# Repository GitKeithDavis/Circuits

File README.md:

# Circuits
Open hardware circuit designs by Keith Davis.

# Licensing and More
Refer to the CERN Open Hardware License v1.2 (OHL) [copy] (cern_ohl_v_1_2.txt) in the root of this Git repo along with this [README] document for licensing, liability, and more.
  
Use of the content in this repo implies your consent to the OHL terms.  The original OHL v1.2 was found [here](<https://www.ohwr.org/project/cernohl/wikis/Documents/CERN-OHL-version-1.2>).

[//]: # (Hide links)

   [OHL]: <https://www.ohwr.org/project/cernohl/wikis/Documents/CERN-OHL-version-1.2>
   [copy]: <https://github.com/GitKeithDavis/Circuits/blob/master/cern_ohl_v_1_2.txt>
   [README]: <https://github.com/GitKeithDavis/Circuits/blob/master/README.md>

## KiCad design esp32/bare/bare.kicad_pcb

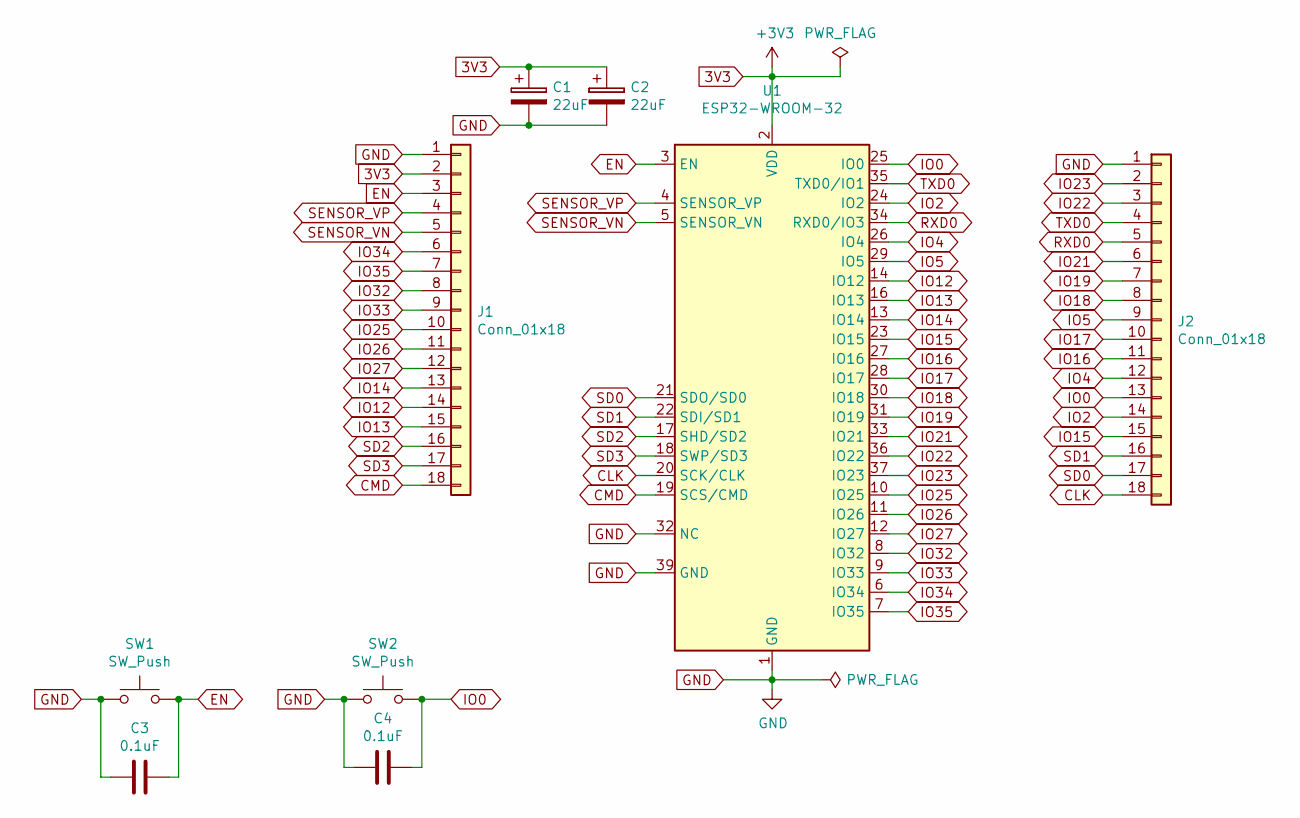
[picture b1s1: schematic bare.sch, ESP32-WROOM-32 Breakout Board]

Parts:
C1, C2: 22uF; C_0805_2012Metric
C3, C4: 0.1uF; C_0805_2012Metric
J1, J2: Conn_01x18; PinHeader_1x18_P2.54mm_Vertical
SW1, SW2: SW_Push; Button_Switch_Push_NO_LCSC_TS5215A160gf
U1: ESP32-WROOM-32

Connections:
3V3: C1.1, C2.1, J1.2, U1.2 (VDD)
CLK: J2.18, U1.20 (SCK/CLK)
CMD: J1.18, U1.19 (SCS/CMD)
EN: C3.1, J1.3, SW1.2, U1.3 (EN)
GND: C1.2, C2.2, C3.2, C4.2, J1.1, J2.1, SW1.1, SW2.1, U1.1 (GND), U1.15 (GND), U1.32 (NC), U1.38 (GND), U1.39 (GND)
IO0: C4.1, J2.13, SW2.2, U1.25 (IO0)
IO2: J2.14, U1.24 (IO2)
IO4: J2.12, U1.26 (IO4)
IO5: J2.9, U1.29 (IO5)
IO12: J1.14, U1.14 (IO12)
IO13: J1.15, U1.16 (IO13)
IO14: J1.13, U1.13 (IO14)
IO15: J2.15, U1.23 (IO15)
IO16: J2.11, U1.27 (IO16)
IO17: J2.10, U1.28 (IO17)
IO18: J2.8, U1.30 (IO18)
IO19: J2.7, U1.31 (IO19)
IO21: J2.6, U1.33 (IO21)
IO22: J2.3, U1.36 (IO22)
IO23: J2.2, U1.37 (IO23)
IO25: J1.10, U1.10 (IO25)
IO26: J1.11, U1.11 (IO26)
IO27: J1.12, U1.12 (IO27)
IO32: J1.8, U1.8 (IO32)
IO33: J1.9, U1.9 (IO33)
IO34: J1.6, U1.6 (IO34)
IO35: J1.7, U1.7 (IO35)
RXD0: J2.5, U1.34 (RXD0/IO3)
SD0: J2.17, U1.21 (SDO/SD0)
SD1: J2.16, U1.22 (SDI/SD1)
SD2: J1.16, U1.17 (SHD/SD2)
SD3: J1.17, U1.18 (SWP/SD3)
SENSOR_VN: J1.5, U1.5 (SENSOR_VN)
SENSOR_VP: J1.4, U1.4 (SENSOR_VP)
TXD0: J2.4, U1.35 (TXD0/IO1)

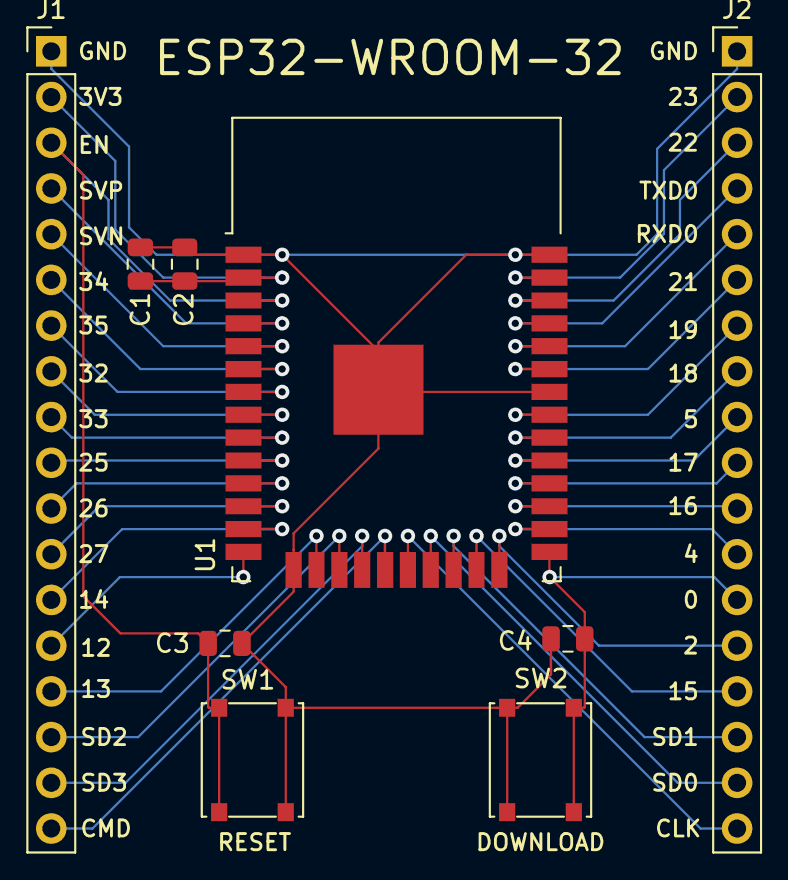
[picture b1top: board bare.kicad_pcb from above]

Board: 2 copper layers, 9 parts (0 on the bottom side), 35 nets.

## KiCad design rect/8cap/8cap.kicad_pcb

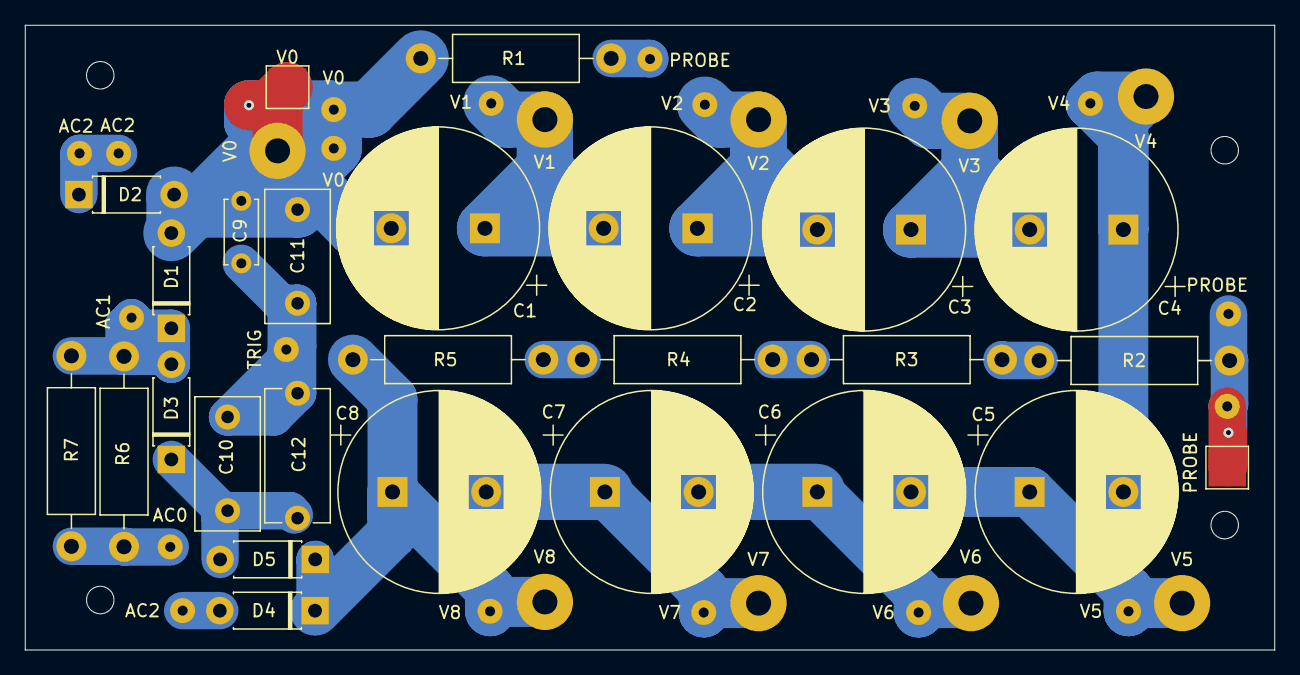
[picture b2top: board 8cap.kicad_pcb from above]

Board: 2 copper layers, 100.0 x 50.0 mm, 54 parts (0 on the bottom side), 18 nets.

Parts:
AC0, AC1, AC2, AC2#2, AC2#3: Conn_01x01_Female; SolderWirePad_1x01_Drill0.8mm
C1, C2, C3, C4, C5, C6, C7, C8: 270u; CP_Radial_D16.0mm_P7.50mm
C9: 1n; C_Disc_D5.0mm_W2.5mm_P5.00mm
C10: 10n; C_Disc_D10.5mm_W5.0mm_P7.50mm
C11: 1n; C_Disc_D10.5mm_W5.0mm_P7.50mm
C12: 10n; C_Disc_D10.5mm_W5.0mm_P10.00mm
D1, D2, D3, D4, D5: R3000; D_DO-41_SOD81_P7.62mm_Horizontal_ref_moved
PROBE: Conn_01x01_Female; SolderWirePad_1x01_Drill0.8mm
PROBE#2, PROBE#4: Conn_01x01_Female; SolderWirePad_1x01_Drill0.8mm
PROBE#3: Conn_01x01_Female; TestPoint_Pad_3.0x3.0mm
R1: 47k; R_Axial_DIN0411_L9.9mm_D3.6mm_P15.24mm_Horizontal
R2, R3, R4, R5: 10meg; R_Axial_DIN0411_L9.9mm_D3.6mm_P15.24mm_Horizontal
R6, R7: 1meg; R_Axial_DIN0411_L9.9mm_D3.6mm_P15.24mm_Horizontal
TRIG: Conn_01x01_Female; SolderWirePad_1x01_Drill0.8mm
V0, V1, V2, V3, V4, V5, V6, V7, V8: Conn_01x01_Female; SolderWirePad_1x01_Drill2mm
V0#2, V0#4, V1#2, V2#2, V3#2, V4#2, V5#2, V6#2, V7#2, V8#2: Conn_01x01_Female; SolderWirePad_1x01_Drill0.8mm
V0#3: Conn_01x01_Female; TestPoint_Pad_3.0x3.0mm

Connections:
AC0: AC0.1, R6.2, R7.1
AC1: AC1.1, D1.1, D3.2, R6.1, R7.2
AC2: AC2.1, AC2#2.1, AC2#3.1, D2.1, D4.2
unnamed: C10.1, C12.1, D3.1, D5.2
unnamed: R2.1, R3.2
unnamed: R3.1, R4.2
unnamed: R4.1, R5.2
PROBE: PROBE.1, PROBE#2.1, PROBE#3.1, PROBE#4.1, R1.1, R2.2
TRIG: C9.1, C10.2, C11.1, C12.2, TRIG.1
V0: C1.2, C9.2, C11.2, D1.2, D2.2, R1.2, V0.1, V0#2.1, V0#3.1, V0#4.1
V1: C1.1, C2.2, V1.1, V1#2.1
V2: C2.1, C3.2, V2.1, V2#2.1
V3: C3.1, C4.2, V3.1, V3#2.1
V4: C4.1, C5.2, V4.1, V4#2.1
V5: C5.1, C6.2, V5.1, V5#2.1
V6: C6.1, C7.2, V6.1, V6#2.1
V7: C7.1, C8.2, V7.1, V7#2.1
V8: C8.1, D4.1, D5.1, R5.1, V8.1, V8#2.1

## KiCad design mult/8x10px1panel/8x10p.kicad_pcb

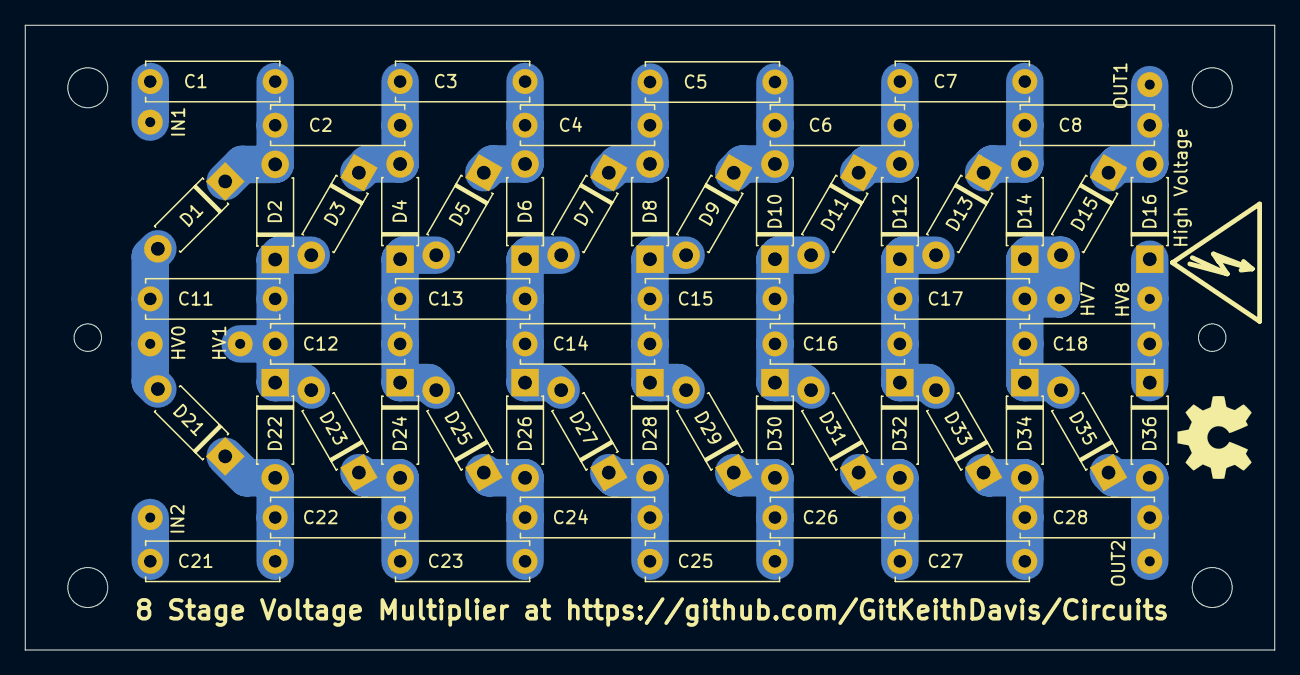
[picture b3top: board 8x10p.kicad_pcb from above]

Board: 2 copper layers, 100.0 x 50.0 mm, 65 parts (0 on the bottom side), 27 nets.

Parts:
C1, C2, C3, C4, C5, C6, C7, C8, C11, C12, C13, C14, C15, C16, C17, C18, C21, C22, C23, C24, C25, C26, C27, C28: 10n; C_Disc_D10.5mm_W2.5mm_P10.00mm
D1, D2, D3, D4, D5, D6, D7, D8, D9, D10, D11, D12, D13, D14, D15, D16, D21, D22, D23, D24, D25, D26, D27, D28, D29, D30, D31, D32, D33, D34, D35, D36: R3000; D_DO-41_SOD81_P7.62mm_Horizontal_ref_moved
HV0, HV1, HV7, HV8: Conn_01x01; SolderWirePad_1x01_Drill0.8mm
High Voltage: Symbol_HighVoltage_Type2_FSilk_Small
IN1, IN2: Conn_01x01; SolderWirePad_1x01_Drill0.8mm
OUT1, OUT2: Conn_01x01; SolderWirePad_1x01_Drill0.8mm

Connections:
/multiplier/HV0: C11.2, D1.2, D21.2, HV0.1
/multiplier/HV1: C11.1, C12.2, D2.1, D3.2, D22.1, D23.2, HV1.1
/multiplier/HV7: C17.1, C18.2, D14.1, D15.2, D34.1, D35.2, HV7.1
/multiplier/HV8: C18.1, D16.1, D36.1, HV8.1
/multiplier/IN1: C1.2, IN1.1
/multiplier/IN2: C21.2, IN2.1
/multiplier/OUT1: C8.1, D15.1, D16.2, OUT1.1
/multiplier/OUT2: C28.1, D35.1, D36.2, OUT2.1
unnamed: C1.1, C2.2, D1.1, D2.2
unnamed: C2.1, C3.2, D3.1, D4.2
unnamed: C3.1, C4.2, D5.1, D6.2
unnamed: C4.1, C5.2, D7.1, D8.2
unnamed: C5.1, C6.2, D9.1, D10.2
unnamed: C6.1, C7.2, D11.1, D12.2
unnamed: C7.1, C8.2, D13.1, D14.2
unnamed: C12.1, C13.2, D4.1, D5.2, D24.1, D25.2
unnamed: C13.1, C14.2, D6.1, D7.2, D26.1, D27.2
unnamed: C14.1, C15.2, D8.1, D9.2, D28.1, D29.2
unnamed: C15.1, C16.2, D10.1, D11.2, D30.1, D31.2
unnamed: C16.1, C17.2, D12.1, D13.2, D32.1, D33.2
unnamed: C21.1, C22.2, D21.1, D22.2
unnamed: C22.1, C23.2, D23.1, D24.2
unnamed: C23.1, C24.2, D25.1, D26.2
unnamed: C24.1, C25.2, D27.1, D28.2
unnamed: C25.1, C26.2, D29.1, D30.2
unnamed: C26.1, C27.2, D31.1, D32.2
unnamed: C27.1, C28.2, D33.1, D34.2

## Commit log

2019-10-09 Added license and README content.
2019-10-09 Changed README to incorp links in remote.
2019-10-09 Added 10x10p, 8x10p multipliers and 8x cap rectifier
2019-10-09 Made single panel mult versions.
2019-10-09 Added 2 panel version of the 8 cap rectifier
2020-03-02 Created v1 of the ESP32 breakout board.
2020-03-02 Renamed bare4x4 to bare4
2020-03-02 Created Gerber and drill files

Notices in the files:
esp32/bare/bare.kicad_pcb:
CERN Open Source Hardware License v1.2
rect/8cap/8cap.kicad_pcb:
Danger: High Voltage!  Open Hardware License v1.2
